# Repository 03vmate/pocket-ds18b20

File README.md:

# pocket-ds18b20
Battery powered DS18B20 thermometer

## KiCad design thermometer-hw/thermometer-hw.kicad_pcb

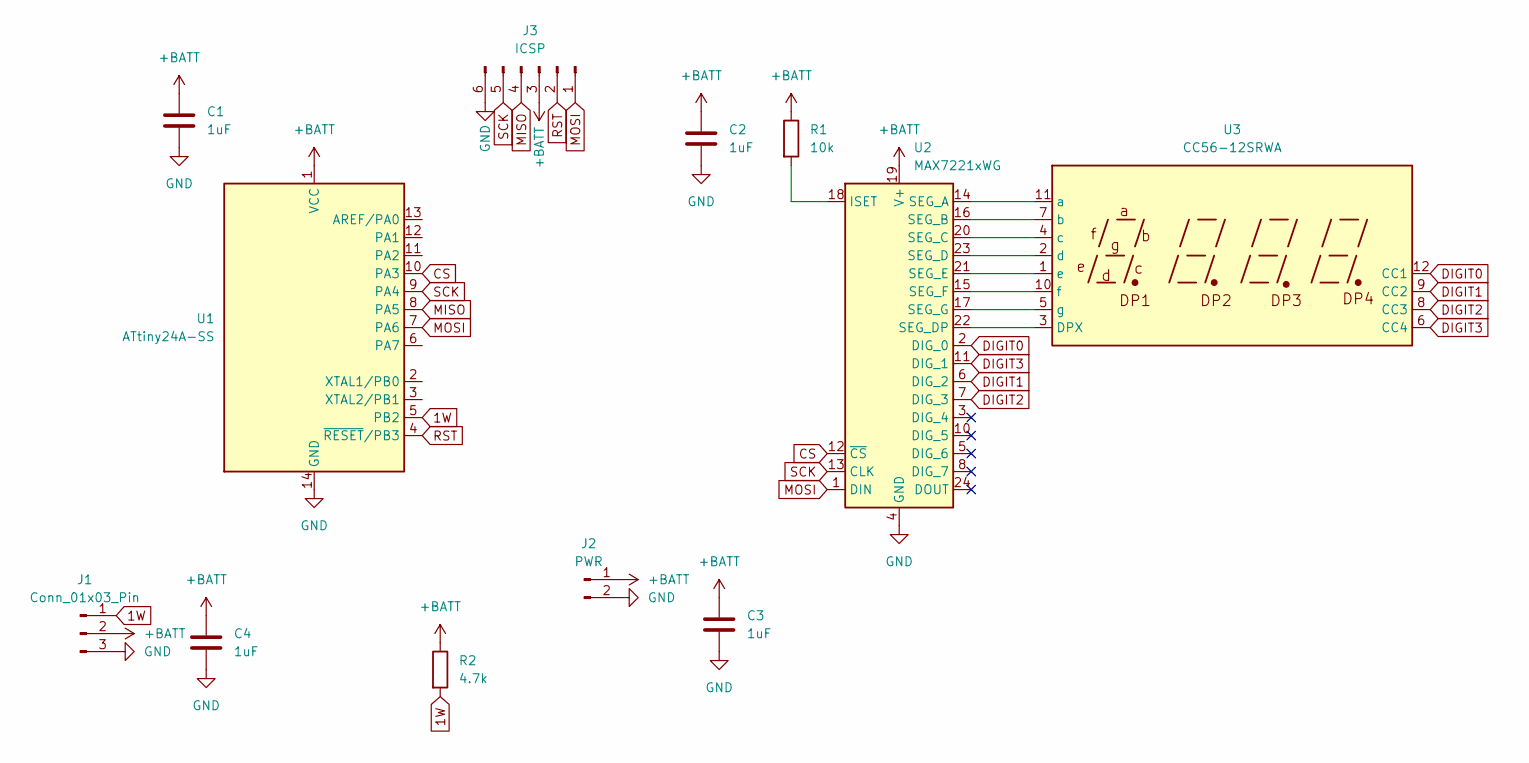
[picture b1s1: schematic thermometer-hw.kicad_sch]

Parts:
C1, C2, C3, C4: 1uF; C_0805_2012Metric_Pad1.18x1.45mm_HandSolder
J1: Conn_01x03_Pin; PinHeader_1x03_P2.00mm_Vertical
J2: PWR; PinHeader_1x02_P2.54mm_Vertical
J3: ICSP; PinHeader_1x06_P2.54mm_Vertical
R1: 10k; R_0805_2012Metric_Pad1.20x1.40mm_HandSolder
R2: 4.7k; R_0805_2012Metric_Pad1.20x1.40mm_HandSolder
U1: ATtiny24A-SS; SOIC-14_3.9x8.7mm_P1.27mm
U2: MAX7221xWG; SOIC-24W_7.5x15.4mm_P1.27mm
U3: CC56-12SRWA; CC56-12GWA

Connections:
1W: J1.1, R2.2, U1.5 (PB2)
+BATT: C1.1, C2.1, C3.1, C4.1, J1.2, J2.1, J3.3, R1.1, R2.1, U1.1 (VCC), U2.19 (V+)
CS: U1.10 (PA3), U2.12 (~CS)
DIGIT0: U2.2 (DIG_0), U3.12 (CC1)
DIGIT1: U2.6 (DIG_2), U3.9 (CC2)
DIGIT2: U2.7 (DIG_3), U3.8 (CC3)
DIGIT3: U2.11 (DIG_1), U3.6 (CC4)
GND: C1.2, C2.2, C3.2, C4.2, J1.3, J2.2, J3.6, U1.14 (GND), U2.4 (GND), U2.9 (GND)
MISO: J3.4, U1.8 (PA5)
MOSI: J3.1, U1.7 (PA6), U2.1 (DIN)
unnamed: R1.2, U2.18 (ISET)
unnamed: U2.14 (SEG_A), U3.11 (a)
unnamed: U2.16 (SEG_B), U3.7 (b)
unnamed: U2.20 (SEG_C), U3.4 (c)
unnamed: U2.23 (SEG_D), U3.2 (d)
unnamed: U2.22 (SEG_DP), U3.3 (DPX)
unnamed: U2.21 (SEG_E), U3.1 (e)
unnamed: U2.15 (SEG_F), U3.10 (f)
unnamed: U2.17 (SEG_G), U3.5 (g)
RST: J3.2, U1.4 (~RESET/PB3)
SCK: J3.5, U1.9 (PA4), U2.13 (CLK)

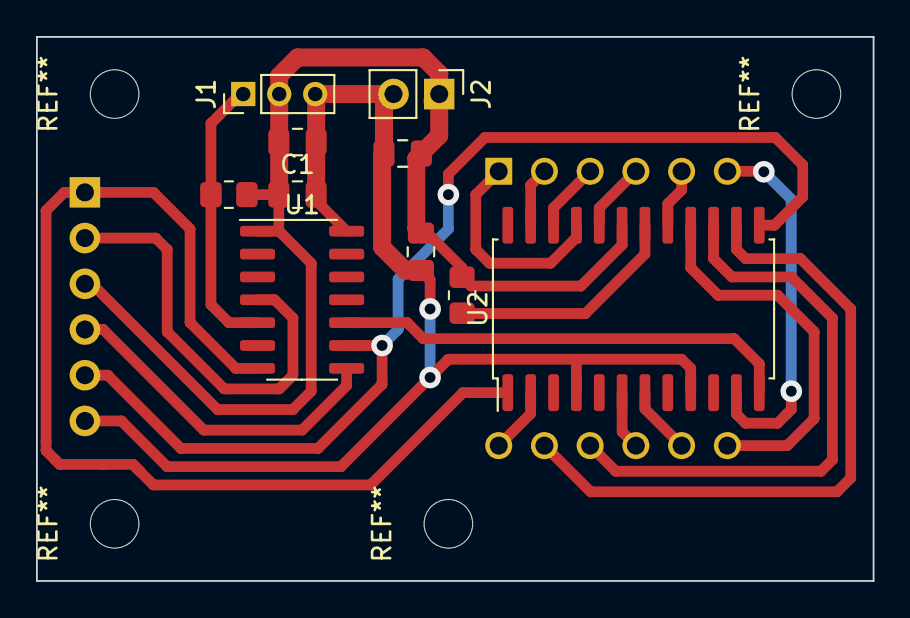
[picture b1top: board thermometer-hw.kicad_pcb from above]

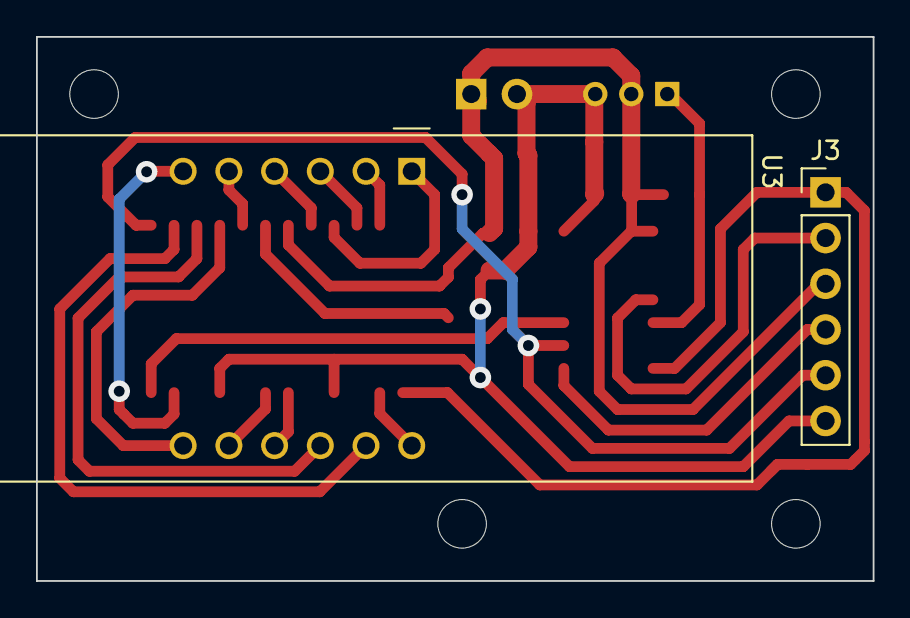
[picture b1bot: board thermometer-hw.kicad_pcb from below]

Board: 2 copper layers, 46.5 x 30.2 mm, 12 parts (2 on the bottom side), 21 nets.

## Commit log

2024-02-07 Schematic and half-done layout
2024-02-07 Final touches and gerbers
2024-09-01 Firmware progress
2024-09-01 Finished fw
